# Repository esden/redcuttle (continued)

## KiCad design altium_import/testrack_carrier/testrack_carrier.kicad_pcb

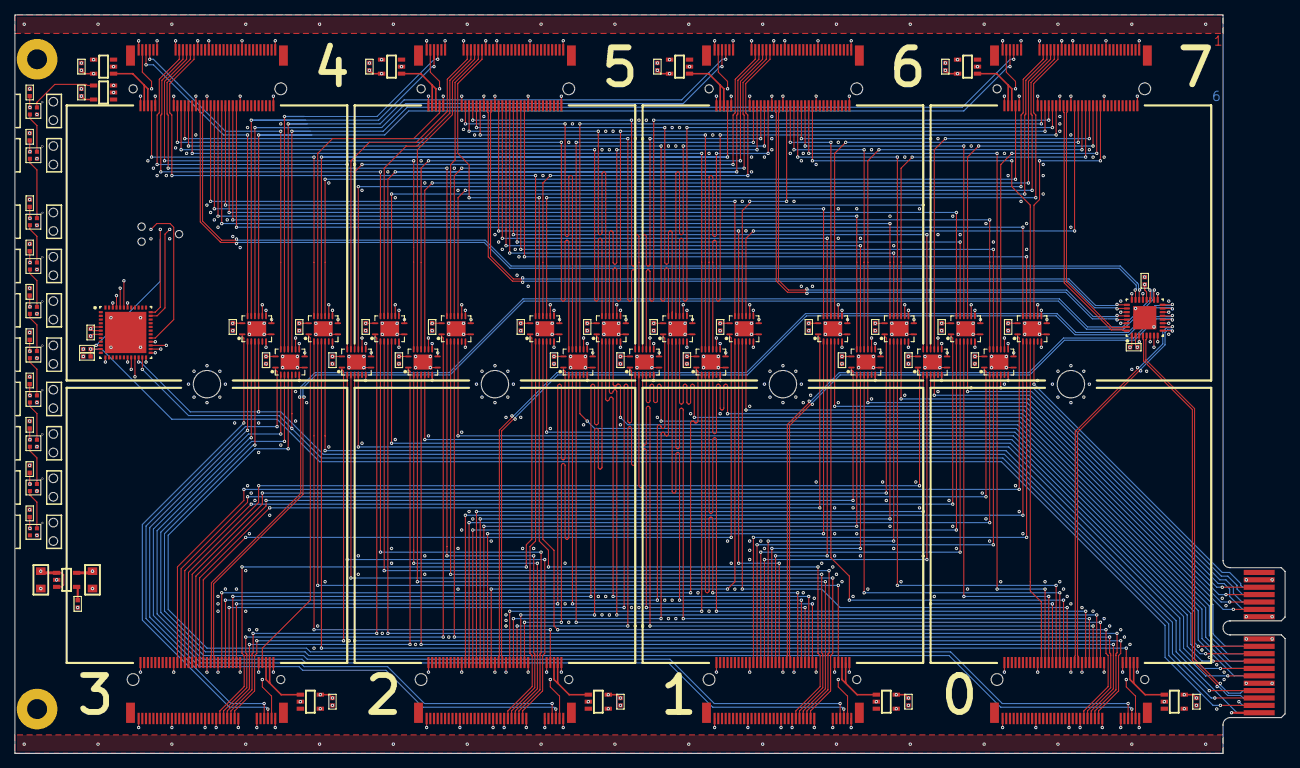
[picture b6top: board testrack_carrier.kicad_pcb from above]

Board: 6 copper layers, 172.0 x 100.0 mm, 115 parts (1 on the bottom side), 248 nets.

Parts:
C1, C2, C3_MUX_GPIO0, C3_MUX_GPIO1, C3_MUX_GPIO2, C3_MUX_GPIO3, C3_MUX_GPIO4, C3_MUX_GPIO5, C3_MUX_GPIO6, C3_MUX_GPIO7, C3_MUX_JTCK, C3_MUX_JTDI, C3_MUX_JTDO, C3_MUX_JTMS, C3_MUX_MGMT_SCL, C3_MUX_MGMT_SDA, C3_MUX_NRST, C3_MUX_TRACECLK, C3_MUX_TRACED0, C3_MUX_TRACED1, C3_MUX_TRACED2, C3_MUX_TRACED3, C3_MUX_VTREF, C4_TARGET1, C4_TARGET2, C4_TARGET3, C4_TARGET4, C4_TARGET5, C4_TARGET6, C4_TARGET7, C4_TARGET8, C5, C6, C9, C10, C11, C12, C13, C14, C15, C16, C17, C18, C19, C20: 100nF; 0402
C7, C8: 22uF; 0805
LED1, LED2, LED3, LED4, LED5, LED6, LED7, LED8, LED9, LED10: SK6805; EC15
LP1, LP2, LP3, LP4, LP5, LP6, LP7, LP8, LP9, LP10: Lightpipe; SLP3-150-100-F
MH1, MH2, MH3, MH4: Mounting_Hole; WA-SMSI_M2.5
P1: PCIE_X1; PCIE_X1_EDGE
P2_TARGET1, P2_TARGET2, P2_TARGET3, P2_TARGET4, P2_TARGET5, P2_TARGET6, P2_TARGET7, P2_TARGET8: M.2_B
P3: SWD-TC2030; TC2030-NL
P4: MAX4999; MAXIM_T3255+4
R1: 10k; 0402
U1_TARGET1, U1_TARGET2, U1_TARGET3, U1_TARGET4, U1_TARGET5, U1_TARGET6, U1_TARGET7, U1_TARGET8: LSW_FLG; SOT23-5
U2: STM32G071CBU; QFN50P690X710X60_HS-49N
U3_MUX_GPIO0, U3_MUX_GPIO1, U3_MUX_GPIO2, U3_MUX_GPIO3, U3_MUX_GPIO4, U3_MUX_GPIO5, U3_MUX_GPIO6, U3_MUX_GPIO7, U3_MUX_JTCK, U3_MUX_JTDI, U3_MUX_JTDO, U3_MUX_JTMS, U3_MUX_MGMT_SCL, U3_MUX_MGMT_SDA, U3_MUX_NRST, U3_MUX_TRACECLK, U3_MUX_TRACED0, U3_MUX_TRACED1, U3_MUX_TRACED2, U3_MUX_TRACED3, U3_MUX_VTREF: SN74CB3Q3251; TI_RGY
U4: SN74LV1T34; SOT23-5
U5: RT9193-33; SOT23-5

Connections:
GND: C1.1, C2.1, C3_MUX_GPIO0.1, C3_MUX_GPIO1.1, C3_MUX_GPIO2.1, C3_MUX_GPIO3.1, C3_MUX_GPIO4.1, C3_MUX_GPIO5.1, C3_MUX_GPIO6.1, C3_MUX_GPIO7.1, C3_MUX_JTCK.1, C3_MUX_JTDI.1, C3_MUX_JTDO.1, C3_MUX_JTMS.1, C3_MUX_MGMT_SCL.1, C3_MUX_MGMT_SDA.1, C3_MUX_NRST.1, C3_MUX_TRACECLK.1, C3_MUX_TRACED0.1, C3_MUX_TRACED1.1, C3_MUX_TRACED2.1, C3_MUX_TRACED3.1, C3_MUX_VTREF.1, C4_TARGET1.1, C4_TARGET2.1, C4_TARGET3.1, C4_TARGET4.1, C4_TARGET5.1, C4_TARGET6.1, C4_TARGET7.1, C4_TARGET8.1, C5.1, C6.1, C7.1, C8.1, C9.1, C10.1, C11.1, C12.1, C13.1, C14.1, C15.1, C16.1, C17.1, C18.1, C19.1, C20.1, LED1.4, LED2.4, LED3.4, LED4.4, LED5.4, LED6.4, LED7.4, LED8.4, LED9.4, LED10.4, MH1.1, MH2.1, MH3.1, MH4.1, P1.A2, P1.A5, P1.A11, P1.A12, P1.A17, P1.B5, P1.B11, P1.B12, P1.B17, P2_TARGET1.1, P2_TARGET1.2, P2_TARGET1.10, P2_TARGET1.11, P2_TARGET1.20, P2_TARGET1.21, P2_TARGET1.32, P2_TARGET1.33, P2_TARGET1.38, P2_TARGET1.39, P2_TARGET1.56, P2_TARGET1.57, P2_TARGET1.74, P2_TARGET1.75, P2_TARGET2.1, P2_TARGET2.2, P2_TARGET2.10, P2_TARGET2.11, P2_TARGET2.20, P2_TARGET2.21, P2_TARGET2.32, P2_TARGET2.33, P2_TARGET2.38, P2_TARGET2.39, P2_TARGET2.56, P2_TARGET2.57, P2_TARGET2.74, P2_TARGET2.75, P2_TARGET3.1, P2_TARGET3.2, P2_TARGET3.10, P2_TARGET3.11, P2_TARGET3.20, P2_TARGET3.21, P2_TARGET3.32, P2_TARGET3.33, P2_TARGET3.38, P2_TARGET3.39, P2_TARGET3.56, P2_TARGET3.57, P2_TARGET3.74, P2_TARGET3.75, P2_TARGET4.1, P2_TARGET4.2, P2_TARGET4.10, P2_TARGET4.11, P2_TARGET4.20, P2_TARGET4.21, P2_TARGET4.32, P2_TARGET4.33, P2_TARGET4.38, P2_TARGET4.39, P2_TARGET4.56, P2_TARGET4.57, P2_TARGET4.74, P2_TARGET4.75, P2_TARGET5.1, P2_TARGET5.2, P2_TARGET5.10, P2_TARGET5.11, P2_TARGET5.20, P2_TARGET5.21, P2_TARGET5.32, P2_TARGET5.33, P2_TARGET5.38, P2_TARGET5.39, P2_TARGET5.56, P2_TARGET5.57, P2_TARGET5.74, P2_TARGET5.75, P2_TARGET6.1, P2_TARGET6.2, P2_TARGET6.10, P2_TARGET6.11, P2_TARGET6.20, P2_TARGET6.21, P2_TARGET6.32, P2_TARGET6.33, P2_TARGET6.38, P2_TARGET6.39, P2_TARGET6.56, P2_TARGET6.57, P2_TARGET6.74, P2_TARGET6.75, P2_TARGET7.1, P2_TARGET7.2, P2_TARGET7.10, P2_TARGET7.11, P2_TARGET7.20, P2_TARGET7.21, P2_TARGET7.32, P2_TARGET7.33, P2_TARGET7.38, P2_TARGET7.39, P2_TARGET7.56, P2_TARGET7.57, P2_TARGET7.74, P2_TARGET7.75, P2_TARGET8.1, P2_TARGET8.2, P2_TARGET8.10, P2_TARGET8.11, P2_TARGET8.20, P2_TARGET8.21, P2_TARGET8.32, P2_TARGET8.33, P2_TARGET8.38, P2_TARGET8.39, P2_TARGET8.56, P2_TARGET8.57, P2_TARGET8.74, P2_TARGET8.75, P3.5, P4.1, P4.11, P4.14, P4.17, P4.21, P4.24, P4.27, P4.30, P4.PAD, U1_TARGET1.2, U1_TARGET2.2, U1_TARGET3.2, U1_TARGET4.2, U1_TARGET5.2, U1_TARGET6.2, U1_TARGET7.2, U1_TARGET8.2, U2.7, U2.PAD, U3_MUX_GPIO0.8, U3_MUX_GPIO0.PAD, U3_MUX_GPIO1.8, U3_MUX_GPIO1.PAD, U3_MUX_GPIO2.8, U3_MUX_GPIO2.PAD, U3_MUX_GPIO3.8, U3_MUX_GPIO3.PAD, U3_MUX_GPIO4.8, U3_MUX_GPIO4.PAD, U3_MUX_GPIO5.8, U3_MUX_GPIO5.PAD, U3_MUX_GPIO6.8, U3_MUX_GPIO6.PAD, U3_MUX_GPIO7.8, U3_MUX_GPIO7.PAD, U3_MUX_JTCK.8, U3_MUX_JTCK.PAD, U3_MUX_JTDI.8, U3_MUX_JTDI.PAD, U3_MUX_JTDO.8, U3_MUX_JTDO.PAD, U3_MUX_JTMS.8, U3_MUX_JTMS.PAD, U3_MUX_MGMT_SCL.8, U3_MUX_MGMT_SCL.PAD, U3_MUX_MGMT_SDA.8, U3_MUX_MGMT_SDA.PAD, U3_MUX_NRST.8, U3_MUX_NRST.PAD, U3_MUX_TRACECLK.8, U3_MUX_TRACECLK.PAD, U3_MUX_TRACED0.8, U3_MUX_TRACED0.PAD, U3_MUX_TRACED1.8, U3_MUX_TRACED1.PAD, U3_MUX_TRACED2.8, U3_MUX_TRACED2.PAD, U3_MUX_TRACED3.8, U3_MUX_TRACED3.PAD, U3_MUX_VTREF.8, U3_MUX_VTREF.PAD, U4.3, U5.2
GPIO0: P1.B13, U3_MUX_GPIO0.5
GPIO1: P1.B14, U3_MUX_GPIO1.5
GPIO01: P2_TARGET1.40, U3_MUX_GPIO0.4
GPIO02: P2_TARGET2.40, U3_MUX_GPIO0.3
GPIO2: P1.B15, U3_MUX_GPIO2.5
GPIO03: P2_TARGET3.40, U3_MUX_GPIO0.2
GPIO3: P1.B16, U3_MUX_GPIO3.5
GPIO04: P2_TARGET4.40, U3_MUX_GPIO0.1
GPIO4: P1.A13, U3_MUX_GPIO4.5
GPIO05: P2_TARGET5.40, U3_MUX_GPIO0.15
GPIO5: P1.A14, U3_MUX_GPIO5.5
GPIO06: P2_TARGET6.40, U3_MUX_GPIO0.14
GPIO6: P1.A15, U3_MUX_GPIO6.5
GPIO07: P2_TARGET7.40, U3_MUX_GPIO0.13
GPIO7: P1.A16, U3_MUX_GPIO7.5
GPIO08: P2_TARGET8.40, U3_MUX_GPIO0.12
GPIO11: P2_TARGET1.42, U3_MUX_GPIO1.4
GPIO12: P2_TARGET2.42, U3_MUX_GPIO1.3
GPIO13: P2_TARGET3.42, U3_MUX_GPIO1.2
GPIO14: P2_TARGET4.42, U3_MUX_GPIO1.1
GPIO15: P2_TARGET5.42, U3_MUX_GPIO1.15
GPIO16: P2_TARGET6.42, U3_MUX_GPIO1.14
GPIO17: P2_TARGET7.42, U3_MUX_GPIO1.13
GPIO18: P2_TARGET8.42, U3_MUX_GPIO1.12
GPIO21: P2_TARGET1.44, U3_MUX_GPIO2.4
GPIO22: P2_TARGET2.44, U3_MUX_GPIO2.3
GPIO23: P2_TARGET3.44, U3_MUX_GPIO2.2
GPIO24: P2_TARGET4.44, U3_MUX_GPIO2.1
GPIO25: P2_TARGET5.44, U3_MUX_GPIO2.15
GPIO26: P2_TARGET6.44, U3_MUX_GPIO2.14
GPIO27: P2_TARGET7.44, U3_MUX_GPIO2.13
GPIO28: P2_TARGET8.44, U3_MUX_GPIO2.12
GPIO31: P2_TARGET1.46, U3_MUX_GPIO3.4
GPIO32: P2_TARGET2.46, U3_MUX_GPIO3.3
GPIO33: P2_TARGET3.46, U3_MUX_GPIO3.2
GPIO34: P2_TARGET4.46, U3_MUX_GPIO3.1
GPIO35: P2_TARGET5.46, U3_MUX_GPIO3.15
GPIO36: P2_TARGET6.46, U3_MUX_GPIO3.14
GPIO37: P2_TARGET7.46, U3_MUX_GPIO3.13
GPIO38: P2_TARGET8.46, U3_MUX_GPIO3.12
GPIO41: P2_TARGET1.48, U3_MUX_GPIO4.4
GPIO42: P2_TARGET2.48, U3_MUX_GPIO4.3
GPIO43: P2_TARGET3.48, U3_MUX_GPIO4.2
GPIO44: P2_TARGET4.48, U3_MUX_GPIO4.1
GPIO45: P2_TARGET5.48, U3_MUX_GPIO4.15
GPIO46: P2_TARGET6.48, U3_MUX_GPIO4.14
GPIO47: P2_TARGET7.48, U3_MUX_GPIO4.13
GPIO48: P2_TARGET8.48, U3_MUX_GPIO4.12
GPIO51: P2_TARGET1.50, U3_MUX_GPIO5.4
GPIO52: P2_TARGET2.50, U3_MUX_GPIO5.3
GPIO53: P2_TARGET3.50, U3_MUX_GPIO5.2
GPIO54: P2_TARGET4.50, U3_MUX_GPIO5.1
GPIO55: P2_TARGET5.50, U3_MUX_GPIO5.15
GPIO56: P2_TARGET6.50, U3_MUX_GPIO5.14
GPIO57: P2_TARGET7.50, U3_MUX_GPIO5.13
GPIO58: P2_TARGET8.50, U3_MUX_GPIO5.12
GPIO61: P2_TARGET1.52, U3_MUX_GPIO6.4
GPIO62: P2_TARGET2.52, U3_MUX_GPIO6.3
GPIO63: P2_TARGET3.52, U3_MUX_GPIO6.2
GPIO64: P2_TARGET4.52, U3_MUX_GPIO6.1
GPIO65: P2_TARGET5.52, U3_MUX_GPIO6.15
GPIO66: P2_TARGET6.52, U3_MUX_GPIO6.14
GPIO67: P2_TARGET7.52, U3_MUX_GPIO6.13
GPIO68: P2_TARGET8.52, U3_MUX_GPIO6.12
GPIO71: P2_TARGET1.54, U3_MUX_GPIO7.4
GPIO72: P2_TARGET2.54, U3_MUX_GPIO7.3
GPIO73: P2_TARGET3.54, U3_MUX_GPIO7.2
GPIO74: P2_TARGET4.54, U3_MUX_GPIO7.1
GPIO75: P2_TARGET5.54, U3_MUX_GPIO7.15
GPIO76: P2_TARGET6.54, U3_MUX_GPIO7.14
GPIO77: P2_TARGET7.54, U3_MUX_GPIO7.13
GPIO78: P2_TARGET8.54, U3_MUX_GPIO7.12
JTCK: P1.B7, U3_MUX_JTCK.5
JTCK1: P2_TARGET1.25, U3_MUX_JTCK.4
JTCK2: P2_TARGET2.25, U3_MUX_JTCK.3
JTCK3: P2_TARGET3.25, U3_MUX_JTCK.2
JTCK4: P2_TARGET4.25, U3_MUX_JTCK.1
JTCK5: P2_TARGET5.25, U3_MUX_JTCK.15
JTCK6: P2_TARGET6.25, U3_MUX_JTCK.14
JTCK7: P2_TARGET7.25, U3_MUX_JTCK.13
JTCK8: P2_TARGET8.25, U3_MUX_JTCK.12
JTDI: P1.B9, U3_MUX_JTDI.5
JTDI1: P2_TARGET1.29, U3_MUX_JTDI.4
JTDI2: P2_TARGET2.29, U3_MUX_JTDI.3
JTDI3: P2_TARGET3.29, U3_MUX_JTDI.2
JTDI4: P2_TARGET4.29, U3_MUX_JTDI.1
JTDI5: P2_TARGET5.29, U3_MUX_JTDI.15
JTDI6: P2_TARGET6.29, U3_MUX_JTDI.14
JTDI7: P2_TARGET7.29, U3_MUX_JTDI.13
JTDI8: P2_TARGET8.29, U3_MUX_JTDI.12
JTDO: P1.B8, U3_MUX_JTDO.5
JTDO1: P2_TARGET1.27, U3_MUX_JTDO.4
JTDO2: P2_TARGET2.27, U3_MUX_JTDO.3
JTDO3: P2_TARGET3.27, U3_MUX_JTDO.2
JTDO4: P2_TARGET4.27, U3_MUX_JTDO.1
JTDO5: P2_TARGET5.27, U3_MUX_JTDO.15
JTDO6: P2_TARGET6.27, U3_MUX_JTDO.14
JTDO7: P2_TARGET7.27, U3_MUX_JTDO.13
JTDO8: P2_TARGET8.27, U3_MUX_JTDO.12
JTMS: P1.B6, U3_MUX_JTMS.5
JTMS1: P2_TARGET1.23, U3_MUX_JTMS.4
JTMS2: P2_TARGET2.23, U3_MUX_JTMS.3
JTMS3: P2_TARGET3.23, U3_MUX_JTMS.2
JTMS4: P2_TARGET4.23, U3_MUX_JTMS.1
JTMS5: P2_TARGET5.23, U3_MUX_JTMS.15
JTMS6: P2_TARGET6.23, U3_MUX_JTMS.14
JTMS7: P2_TARGET7.23, U3_MUX_JTMS.13
JTMS8: P2_TARGET8.23, U3_MUX_JTMS.12
LEDS: U2.13, U4.2
MGMT_ADDR: C2.2, P1.B2, R1.1, U2.11
MGMT_SCL: P1.B4, U2.22, U3_MUX_MGMT_SCL.5
MGMT_SCL1: P2_TARGET1.5, U3_MUX_MGMT_SCL.4
MGMT_SCL2: P2_TARGET2.5, U3_MUX_MGMT_SCL.3
MGMT_SCL3: P2_TARGET3.5, U3_MUX_MGMT_SCL.2
MGMT_SCL4: P2_TARGET4.5, U3_MUX_MGMT_SCL.1
MGMT_SCL5: P2_TARGET5.5, U3_MUX_MGMT_SCL.15
MGMT_SCL6: P2_TARGET6.5, U3_MUX_MGMT_SCL.14
MGMT_SCL7: P2_TARGET7.5, U3_MUX_MGMT_SCL.13
MGMT_SCL8: P2_TARGET8.5, U3_MUX_MGMT_SCL.12
MGMT_SDA: P1.B3, U2.23, U3_MUX_MGMT_SDA.5
MGMT_SDA1: P2_TARGET1.7, U3_MUX_MGMT_SDA.4
MGMT_SDA2: P2_TARGET2.7, U3_MUX_MGMT_SDA.3
MGMT_SDA3: P2_TARGET3.7, U3_MUX_MGMT_SDA.2
MGMT_SDA4: P2_TARGET4.7, U3_MUX_MGMT_SDA.1
MGMT_SDA5: P2_TARGET5.7, U3_MUX_MGMT_SDA.15
MGMT_SDA6: P2_TARGET6.7, U3_MUX_MGMT_SDA.14
MGMT_SDA7: P2_TARGET7.7, U3_MUX_MGMT_SDA.13
MGMT_SDA8: P2_TARGET8.7, U3_MUX_MGMT_SDA.12
MUX_EN: U2.24, U3_MUX_GPIO0.7, U3_MUX_GPIO1.7, U3_MUX_GPIO2.7, U3_MUX_GPIO3.7, U3_MUX_GPIO4.7, U3_MUX_GPIO5.7, U3_MUX_GPIO6.7, U3_MUX_GPIO7.7, U3_MUX_JTCK.7, U3_MUX_JTDI.7, U3_MUX_JTDO.7, U3_MUX_JTMS.7, U3_MUX_MGMT_SCL.7, U3_MUX_MGMT_SDA.7, U3_MUX_NRST.7, U3_MUX_TRACECLK.7, U3_MUX_TRACED0.7, U3_MUX_TRACED1.7, U3_MUX_TRACED2.7, U3_MUX_TRACED3.7, U3_MUX_VTREF.7
MUX_SEL0: P4.6, U2.25, U3_MUX_GPIO0.11, U3_MUX_GPIO1.11, U3_MUX_GPIO2.11, U3_MUX_GPIO3.11, U3_MUX_GPIO4.11, U3_MUX_GPIO5.11, U3_MUX_GPIO6.11, U3_MUX_GPIO7.11, U3_MUX_JTCK.11, U3_MUX_JTDI.11, U3_MUX_JTDO.11, U3_MUX_JTMS.11, U3_MUX_MGMT_SCL.11, U3_MUX_MGMT_SDA.11, U3_MUX_NRST.11, U3_MUX_TRACECLK.11, U3_MUX_TRACED0.11, U3_MUX_TRACED1.11, U3_MUX_TRACED2.11, U3_MUX_TRACED3.11, U3_MUX_VTREF.11
MUX_SEL1: P4.7, U2.26, U3_MUX_GPIO0.10, U3_MUX_GPIO1.10, U3_MUX_GPIO2.10, U3_MUX_GPIO3.10, U3_MUX_GPIO4.10, U3_MUX_GPIO5.10, U3_MUX_GPIO6.10, U3_MUX_GPIO7.10, U3_MUX_JTCK.10, U3_MUX_JTDI.10, U3_MUX_JTDO.10, U3_MUX_JTMS.10, U3_MUX_MGMT_SCL.10, U3_MUX_MGMT_SDA.10, U3_MUX_NRST.10, U3_MUX_TRACECLK.10, U3_MUX_TRACED0.10, U3_MUX_TRACED1.10, U3_MUX_TRACED2.10, U3_MUX_TRACED3.10, U3_MUX_VTREF.10
MUX_SEL2: P4.8, U2.27, U3_MUX_GPIO0.9, U3_MUX_GPIO1.9, U3_MUX_GPIO2.9, U3_MUX_GPIO3.9, U3_MUX_GPIO4.9, U3_MUX_GPIO5.9, U3_MUX_GPIO6.9, U3_MUX_GPIO7.9, U3_MUX_JTCK.9, U3_MUX_JTDI.9, U3_MUX_JTDO.9, U3_MUX_JTMS.9, U3_MUX_MGMT_SCL.9, U3_MUX_MGMT_SDA.9, U3_MUX_NRST.9, U3_MUX_TRACECLK.9, U3_MUX_TRACED0.9, U3_MUX_TRACED1.9, U3_MUX_TRACED2.9, U3_MUX_TRACED3.9, U3_MUX_VTREF.9
MUX_USB_EN: P4.3, U2.28
M_NRST: P3.3, U2.10
NRST: P1.B10, U3_MUX_NRST.5
NRST1: P2_TARGET1.31, U3_MUX_NRST.4
NRST2: P2_TARGET2.31, U3_MUX_NRST.3
NRST3: P2_TARGET3.31, U3_MUX_NRST.2
NRST4: P2_TARGET4.31, U3_MUX_NRST.1
NRST5: P2_TARGET5.31, U3_MUX_NRST.15
NRST6: P2_TARGET6.31, U3_MUX_NRST.14
NRST7: P2_TARGET7.31, U3_MUX_NRST.13
NRST8: P2_TARGET8.31, U3_MUX_NRST.12
NetC20_2: C20.2, U5.4
NetLED1_1: LED1.1, U4.4
NetLED1_3: LED1.3, LED2.1
NetLED2_3: LED2.3, LED3.1
NetLED3_3: LED3.3, LED4.1
NetLED4_3: LED4.3, LED5.1
NetLED5_3: LED5.3, LED6.1
NetLED6_3: LED6.3, LED7.1
NetLED7_3: LED7.3, LED8.1
NetLED8_3: LED8.3, LED9.1
NetLED9_3: LED9.3, LED10.1
PWR_EN1: U1_TARGET1.4, U2.19
PWR_EN2: U1_TARGET2.4, U2.20
PWR_EN3: U1_TARGET3.4, U2.21
PWR_EN4: U1_TARGET4.4, U2.42
PWR_EN5: U1_TARGET5.4, U2.43
PWR_EN6: U1_TARGET6.4, U2.44
PWR_EN7: U1_TARGET7.4, U2.45
PWR_EN8: U1_TARGET8.4, U2.46
SWCLK: P3.4, U2.36
SWDIO: P3.2, U2.35
TRACECLK: P1.A6, U3_MUX_TRACECLK.5
TRACECLK1: P2_TARGET1.22, U3_MUX_TRACECLK.4
TRACECLK2: P2_TARGET2.22, U3_MUX_TRACECLK.3
TRACECLK3: P2_TARGET3.22, U3_MUX_TRACECLK.2
TRACECLK4: P2_TARGET4.22, U3_MUX_TRACECLK.1
TRACECLK5: P2_TARGET5.22, U3_MUX_TRACECLK.15
TRACECLK6: P2_TARGET6.22, U3_MUX_TRACECLK.14
TRACECLK7: P2_TARGET7.22, U3_MUX_TRACECLK.13
TRACECLK8: P2_TARGET8.22, U3_MUX_TRACECLK.12
TRACED0: P1.A7, U3_MUX_TRACED0.5
TRACED1: P1.A8, U3_MUX_TRACED1.5
TRACED01: P2_TARGET1.24, U3_MUX_TRACED0.4
TRACED2: P1.A9, U3_MUX_TRACED2.5
TRACED02: P2_TARGET2.24, U3_MUX_TRACED0.3
TRACED3: P1.A10, U3_MUX_TRACED3.5
TRACED03: P2_TARGET3.24, U3_MUX_TRACED0.2
TRACED04: P2_TARGET4.24, U3_MUX_TRACED0.1
TRACED05: P2_TARGET5.24, U3_MUX_TRACED0.15
TRACED06: P2_TARGET6.24, U3_MUX_TRACED0.14
TRACED07: P2_TARGET7.24, U3_MUX_TRACED0.13
TRACED08: P2_TARGET8.24, U3_MUX_TRACED0.12
TRACED11: P2_TARGET1.26, U3_MUX_TRACED1.4
TRACED12: P2_TARGET2.26, U3_MUX_TRACED1.3
TRACED13: P2_TARGET3.26, U3_MUX_TRACED1.2
TRACED14: P2_TARGET4.26, U3_MUX_TRACED1.1
TRACED15: P2_TARGET5.26, U3_MUX_TRACED1.15
TRACED16: P2_TARGET6.26, U3_MUX_TRACED1.14
TRACED17: P2_TARGET7.26, U3_MUX_TRACED1.13
TRACED18: P2_TARGET8.26, U3_MUX_TRACED1.12
TRACED21: P2_TARGET1.28, U3_MUX_TRACED2.4
TRACED22: P2_TARGET2.28, U3_MUX_TRACED2.3
TRACED23: P2_TARGET3.28, U3_MUX_TRACED2.2
TRACED24: P2_TARGET4.28, U3_MUX_TRACED2.1
TRACED25: P2_TARGET5.28, U3_MUX_TRACED2.15
TRACED26: P2_TARGET6.28, U3_MUX_TRACED2.14
TRACED27: P2_TARGET7.28, U3_MUX_TRACED2.13
TRACED28: P2_TARGET8.28, U3_MUX_TRACED2.12
TRACED31: P2_TARGET1.30, U3_MUX_TRACED3.4
TRACED32: P2_TARGET2.30, U3_MUX_TRACED3.3
TRACED33: P2_TARGET3.30, U3_MUX_TRACED3.2
TRACED34: P2_TARGET4.30, U3_MUX_TRACED3.1
TRACED35: P2_TARGET5.30, U3_MUX_TRACED3.15
TRACED36: P2_TARGET6.30, U3_MUX_TRACED3.14
TRACED37: P2_TARGET7.30, U3_MUX_TRACED3.13
TRACED38: P2_TARGET8.30, U3_MUX_TRACED3.12
UART_TX: P3.6, U2.29
USB_D_N: P1.A4, P4.5
USB_D_N1: P2_TARGET1.36, P4.10
USB_D_N2: P2_TARGET2.36, P4.13
USB_D_N3: P2_TARGET3.36, P4.16
USB_D_N4: P2_TARGET4.36, P4.19
USB_D_N5: P2_TARGET5.36, P4.22
USB_D_N6: P2_TARGET6.36, P4.25
USB_D_N7: P2_TARGET7.36, P4.28
USB_D_N8: P2_TARGET8.36, P4.31
USB_D_P: P1.A3, P4.4
USB_D_P1: P2_TARGET1.34, P4.9
USB_D_P2: P2_TARGET2.34, P4.12
USB_D_P3: P2_TARGET3.34, P4.15
USB_D_P4: P2_TARGET4.34, P4.18
USB_D_P5: P2_TARGET5.34, P4.23
USB_D_P6: P2_TARGET6.34, P4.26
USB_D_P7: P2_TARGET7.34, P4.29
USB_D_P8: P2_TARGET8.34, P4.32
V3.3: C1.2, C3_MUX_GPIO0.2, C3_MUX_GPIO1.2, C3_MUX_GPIO2.2, C3_MUX_GPIO3.2, C3_MUX_GPIO4.2, C3_MUX_GPIO5.2, C3_MUX_GPIO6.2, C3_MUX_GPIO7.2, C3_MUX_JTCK.2, C3_MUX_JTDI.2, C3_MUX_JTDO.2, C3_MUX_JTMS.2, C3_MUX_MGMT_SCL.2, C3_MUX_MGMT_SDA.2, C3_MUX_NRST.2, C3_MUX_TRACECLK.2, C3_MUX_TRACED0.2, C3_MUX_TRACED1.2, C3_MUX_TRACED2.2, C3_MUX_TRACED3.2, C3_MUX_VTREF.2, C5.2, C6.2, C8.2, P2_TARGET1.3, P2_TARGET2.3, P2_TARGET3.3, P2_TARGET4.3, P2_TARGET5.3, P2_TARGET6.3, P2_TARGET7.3, P2_TARGET8.3, P3.1, P4.2, P4.20, R1.2, U2.5, U2.6, U3_MUX_GPIO0.16, U3_MUX_GPIO1.16, U3_MUX_GPIO2.16, U3_MUX_GPIO3.16, U3_MUX_GPIO4.16, U3_MUX_GPIO5.16, U3_MUX_GPIO6.16, U3_MUX_GPIO7.16, U3_MUX_JTCK.16, U3_MUX_JTDI.16, U3_MUX_JTDO.16, U3_MUX_JTMS.16, U3_MUX_MGMT_SCL.16, U3_MUX_MGMT_SDA.16, U3_MUX_NRST.16, U3_MUX_TRACECLK.16, U3_MUX_TRACED0.16, U3_MUX_TRACED1.16, U3_MUX_TRACED2.16, U3_MUX_TRACED3.16, U3_MUX_VTREF.16, U5.5
V5: C4_TARGET1.2, C4_TARGET2.2, C4_TARGET3.2, C4_TARGET4.2, C4_TARGET5.2, C4_TARGET6.2, C4_TARGET7.2, C4_TARGET8.2, C7.2, C9.2, C10.2, C11.2, C12.2, C13.2, C14.2, C15.2, C16.2, C17.2, C18.2, C19.2, LED1.2, LED2.2, LED3.2, LED4.2, LED5.2, LED6.2, LED7.2, LED8.2, LED9.2, LED10.2, P1.B1, U1_TARGET1.5, U1_TARGET2.5, U1_TARGET3.5, U1_TARGET4.5, U1_TARGET5.5, U1_TARGET6.5, U1_TARGET7.5, U1_TARGET8.5, U4.5, U5.1, U5.3
VIN_TARGET1: P2_TARGET1.4, P2_TARGET1.6, U1_TARGET1.1
VIN_TARGET2: P2_TARGET2.4, P2_TARGET2.6, U1_TARGET2.1
VIN_TARGET3: P2_TARGET3.4, P2_TARGET3.6, U1_TARGET3.1
VIN_TARGET4: P2_TARGET4.4, P2_TARGET4.6, U1_TARGET4.1
VIN_TARGET5: P2_TARGET5.4, P2_TARGET5.6, U1_TARGET5.1
VIN_TARGET6: P2_TARGET6.4, P2_TARGET6.6, U1_TARGET6.1
VIN_TARGET7: P2_TARGET7.4, P2_TARGET7.6, U1_TARGET7.1
VIN_TARGET8: P2_TARGET8.4, P2_TARGET8.6, U1_TARGET8.1
VTREF: P1.A1, U3_MUX_VTREF.5
VTREF1: P2_TARGET1.8, U3_MUX_VTREF.4
VTREF2: P2_TARGET2.8, U3_MUX_VTREF.3
VTREF3: P2_TARGET3.8, U3_MUX_VTREF.2
VTREF4: P2_TARGET4.8, U3_MUX_VTREF.1
VTREF5: P2_TARGET5.8, U3_MUX_VTREF.15
VTREF6: P2_TARGET6.8, U3_MUX_VTREF.14
VTREF7: P2_TARGET7.8, U3_MUX_VTREF.13
VTREF8: P2_TARGET8.8, U3_MUX_VTREF.12

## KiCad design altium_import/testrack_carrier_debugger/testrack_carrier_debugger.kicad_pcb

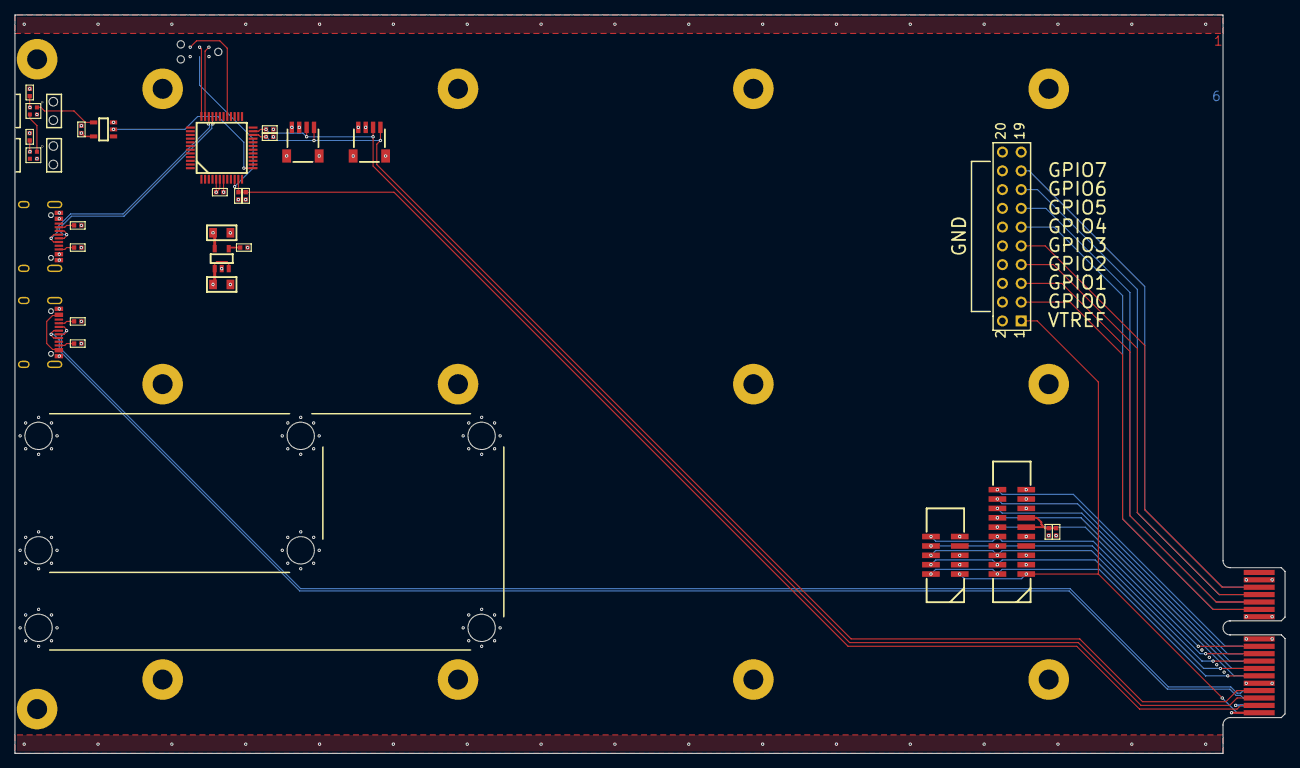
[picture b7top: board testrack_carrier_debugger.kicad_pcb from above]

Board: 6 copper layers, 172.0 x 100.0 mm, 40 parts (1 on the bottom side), 43 nets.

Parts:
C1, C2, C3, C4, C9, C10, C11: 100nF; 0402
C7, C8: 22uF; 0805
LED1, LED2: SK6805; EC15
LP1, LP2: Lightpipe; SLP3-150-100-F
MH1, MH2, MH3, MH4, MH5, MH6, MH7: Mounting_Hole; WA-SMSI_M2.5
P1: PCIE_X1; PCIE_X1_EDGE
P2, P6: USBC; U262-161N-4BVC11
P3: SWD-TC2030; TC2030-NL
P4: SWD-TRACE-FTSH110; FTSH110
P5: SWD-FTSH105; FTSH105
P7, P8: SH4_I2C; SM04B
P9: Header 10X2; HDR2X10
R1: 10k; 0402
R2: NP; 0402
R3, R4, R5, R6: 5.1k; 0402
R7, R8: 2k; 0402
U2: STM32G0B1C; QFP48
U4: SN74LV1T34; SOT23-5
U5: RT9193-33; SOT23-5

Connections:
ADDR: C2.2, P1.B2, R1.1, U2.11
D_N: P1.A4, P6.A7, P6.B7
D_P: P1.A3, P6.A6, P6.B6
GND: C1.1, C2.1, C3.1, C4.1, C7.1, C8.1, C9.1, C10.1, C11.1, LED1.4, LED2.4, P1.A2, P1.A5, P1.A11, P1.A12, P1.A17, P1.B5, P1.B11, P1.B12, P1.B17, P2.A1, P2.A12, P2.B1, P2.B12, P2.SH, P3.5, P4.3, P4.5, P4.9, P4.15, P4.17, P4.19, P5.3, P5.5, P5.9, P6.A1, P6.A12, P6.B1, P6.B12, P6.SH, P7.1, P7.SH, P8.1, P8.SH, P9.4, P9.6, P9.8, P9.10, P9.12, P9.14, P9.16, P9.18, R3.1, R4.1, R5.1, R6.1, U2.7, U4.3, U5.2
GPIO0: P1.B13, P9.3
GPIO1: P1.B14, P9.5
GPIO2: P1.B15, P9.7
GPIO3: P1.B16, P9.9
GPIO4: P1.A13, P9.11
GPIO5: P1.A14, P9.13
GPIO6: P1.A15, P9.15
GPIO7: P1.A16, P9.17
JTCK: P1.B7, P4.4, P5.4
JTDI: P1.B9, P4.8, P5.8
JTDO: P1.B8, P4.6, P5.6
JTMS: P1.B6, P4.2, P5.2
LEDS: U2.13, U4.2
MGMT_SCL: P1.B4, P7.4, P8.4, R8.1, U2.22
MGMT_SDA: P1.B3, P7.3, P8.3, R7.1, U2.23
M_NRST: P3.3, U2.10
M_USB_D_N: P2.A7, P2.B7, U2.33
M_USB_D_P: P2.A6, P2.B6, U2.34
NRST: P1.B10, P4.10, P5.10
NetC3_2: C3.2, P4.11, P4.13, R2.1
NetC4_2: C4.2, U5.4
NetLED1_1: LED1.1, U4.4
NetLED1_3: LED1.3, LED2.1
NetP2_A5: P2.A5, R5.2
NetP2_B5: P2.B5, R6.2
NetP6_A4: P6.A4, P6.A9, P6.B4, P6.B9
NetP6_A5: P6.A5, R3.2
NetP6_B5: P6.B5, R4.2
SWCLK: P3.4, U2.36
SWDIO: P3.2, U2.35
TRACECLK: P1.A6, P4.12
TRACED0: P1.A7, P4.14
TRACED1: P1.A8, P4.16
TRACED2: P1.A9, P4.18
TRACED3: P1.A10, P4.20
UART_TX: P3.6, U2.29
V3.3: C1.2, C8.2, P3.1, P7.2, P8.2, R1.2, R7.2, R8.2, U2.5, U2.6, U5.5
V5: C7.2, C9.2, C10.2, C11.2, LED1.2, LED2.2, P1.B1, P2.A4, P2.A9, P2.B4, P2.B9, R2.2, U4.5, U5.1, U5.3
VTREF: P1.A1, P4.1, P5.1, P9.1

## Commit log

2022-07-17 Initial commit.
2025-01-17 Added all the boards designed by @zyp as reference.
    The boards are converted from the altium originals into KiCad on best
    effort basis. Some data is lost in the conversion.
2025-01-19 Added PKL submodule.
2025-01-19 Added red_cuttle backplane connector symbol.
2025-01-19 Added *.bak to gitignore.
2025-01-19 Initial commit of half rack passive 4u1x backplane.
2025-01-19 Updated the RAddr values. Made USB a diff pair.
2025-01-19 Filleted the tracks.
2025-01-19 Added design credit to @Zyp Thank you! :D
2025-01-19 Added backplane address resistor calculation spreadsheet.
